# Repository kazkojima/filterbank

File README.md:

# HF filter bamk

KiCad files for a simple HF filter bank.

There are 4 5-order Chebyshev bandpass filters for 0.5-2, 2-10, 10-28, 28-45MHz.
 [Actual characteristics](https://github.com/kazkojima/filterbank/blob/main/images/Figure_1.png) deviate slightly from target values.

A filter is selected with an analog demultiplexer/multiplexer TS3A5017PWR of which select inputs are drived with photo-isolators.

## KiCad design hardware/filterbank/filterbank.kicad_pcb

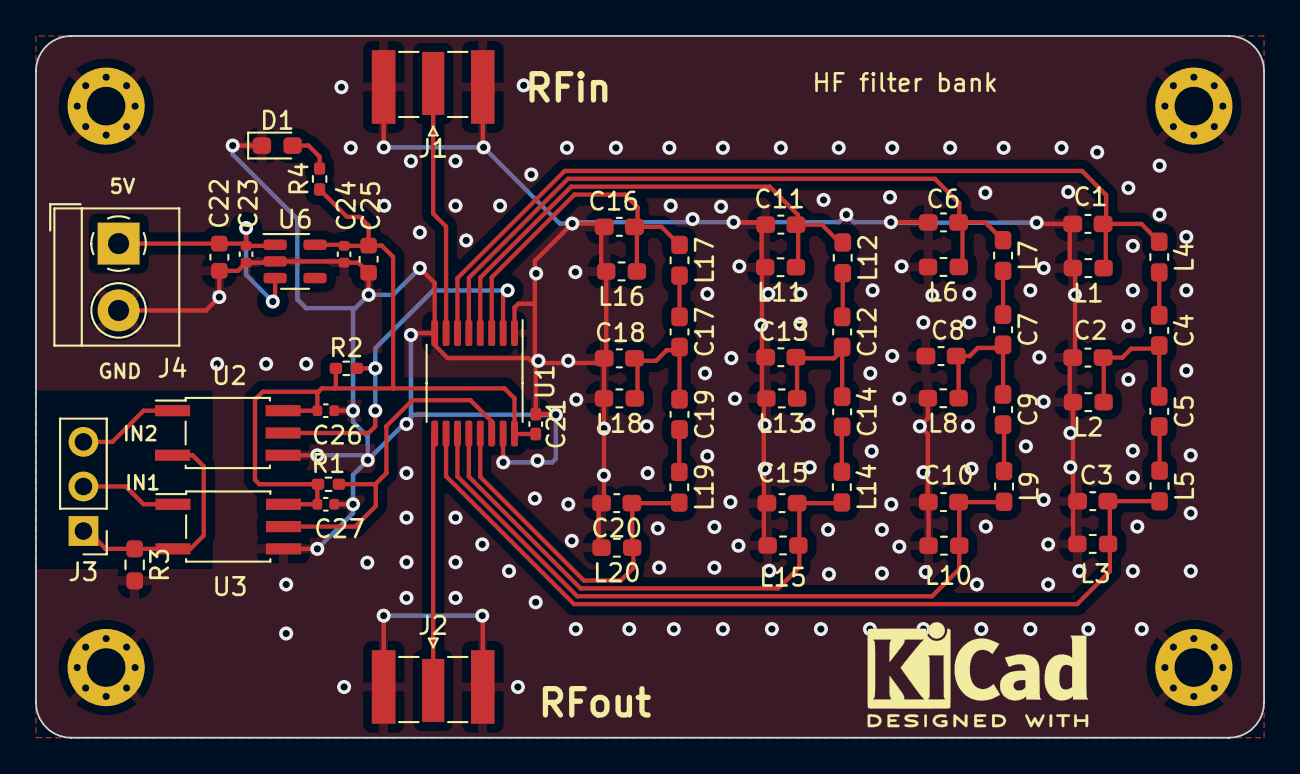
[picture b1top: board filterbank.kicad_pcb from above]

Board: 2 copper layers, 70.0 x 40.0 mm, 64 parts (0 on the bottom side), 31 nets.

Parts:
C1, C3: 2200p; C_0603_1608Metric_Pad1.08x0.95mm_HandSolder
C2: 3900p; C_0603_1608Metric_Pad1.08x0.95mm_HandSolder
C4, C5: 3300p; C_0603_1608Metric_Pad1.08x0.95mm_HandSolder
C6, C10: 470p; C_0603_1608Metric_Pad1.08x0.95mm_HandSolder
C7, C9: 1000p; C_0603_1608Metric_Pad1.08x0.95mm_HandSolder
C8: 820p; C_0603_1608Metric_Pad1.08x0.95mm_HandSolder
C11, C15, C16, C20: 180p; C_0603_1608Metric_Pad1.08x0.95mm_HandSolder
C12, C14: 150p; C_0603_1608Metric_Pad1.08x0.95mm_HandSolder
C13, C18: 330p; C_0603_1608Metric_Pad1.08x0.95mm_HandSolder
C17, C19: 33p; C_0603_1608Metric_Pad1.08x0.95mm_HandSolder
C21: 0.1u; C_0402_1005Metric_Pad0.74x0.62mm_HandSolder
C22, C25: 10u; C_0603_1608Metric
C23, C24: 1u; C_0402_1005Metric
C26, C27: 0.1u; C_0402_1005Metric
D1: LED_Filled; LED_0603_1608Metric_Pad1.05x0.95mm_HandSolder
H1, H2, H3, H4: MountingHole_Pad; MountingHole_2.2mm_M2_Pad_Via
J1, J2: Conn_Coaxial; SMA_Samtec_SMA-J-P-X-ST-EM1_EdgeMount
J3: Conn_01x03; PinHeader_1x03_P2.54mm_Vertical
J4: Screw_Terminal_01x02; TerminalBlock3.81mm
L1, L3: 10uH; L_0603_1608Metric_Pad1.05x0.95mm_HandSolder
L2: 5.6uH; L_0603_1608Metric_Pad1.05x0.95mm_HandSolder
L4, L5: 6.8uH; L_0603_1608Metric_Pad1.05x0.95mm_HandSolder
L6, L10: 2.7uH; L_0603_1608Metric_Pad1.05x0.95mm_HandSolder
L7, L8, L9: 1.5uH; L_0603_1608Metric_Pad1.05x0.95mm_HandSolder
L11, L15: 470nH; L_0603_1608Metric_Pad1.05x0.95mm_HandSolder
L12, L14, L17, L19: 560nH; L_0603_1608Metric_Pad1.05x0.95mm_HandSolder
L13: 270nH; L_0603_1608Metric_Pad1.05x0.95mm_HandSolder
L16, L20: 100nH; L_0603_1608Metric_Pad1.05x0.95mm_HandSolder
L18: 56nH; L_0603_1608Metric_Pad1.05x0.95mm_HandSolder
R1, R2: 4.99k; R_0402_1005Metric_Pad0.72x0.64mm_HandSolder
R3: 10M; R_0603_1608Metric_Pad0.98x0.95mm_HandSolder
R4: 3k; R_0402_1005Metric_Pad0.72x0.64mm_HandSolder
U1: TS3A5017PWR; TSSOP-16_4.4x5mm_P0.65mm
U2, U3: TLP2368; SO-5_4.4x3.6mm_P1.27mm
U6: ADP151AUJZ-3.3; TSOT-23-5

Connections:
+3V3: C21.2, C24.1, C25.1, C26.1, C27.1, R1.1, R2.1, R4.1, U1.16 (V+), U2.6 (VDD), U3.6 (VDD), U6.5 (VOUT)
F1OUT: C3.1, L3.1, L5.2, U1.10 (2S1)
F2OUT: C10.1, L9.2, L10.1, U1.11 (2S2)
F3OUT: C15.1, L14.2, L15.1, U1.12 (2S3)
F4OUT: C20.1, L19.2, L20.1, U1.13 (2S4)
GND: C1.2, C2.2, C3.2, C6.2, C8.2, C10.2, C11.2, C13.2, C15.2, C16.2, C18.2, C20.2, C21.1, C22.2, C23.2, C24.2, C25.2, C26.2, C27.2, D1.1 (K), H1.1, H2.1, H3.1, H4.1, J1.2 (Ext), J2.2 (Ext), J4.2, L1.2, L2.2, L3.2, L6.2, L8.2, L10.2, L11.2, L13.2, L15.2, L16.2, L18.2, L20.2, R3.2, U1.1 (1~EN), U1.8 (GND), U1.15 (2~EN), U2.4 (GND), U3.4 (GND), U6.2 (GND)
unnamed: C2.1, C4.2, C5.1, L2.1
unnamed: C4.1, L4.2
unnamed: C5.2, L5.1
unnamed: C7.1, L7.2
unnamed: C7.2, C8.1, C9.1, L8.1
unnamed: C9.2, L9.1
unnamed: C12.1, L12.2
unnamed: C12.2, C13.1, C14.1, L13.1
unnamed: C14.2, L14.1
unnamed: C17.1, L17.2
unnamed: C17.2, C18.1, C19.1, L18.1
unnamed: C19.2, L19.1
unnamed: D1.2 (A), R4.2
unnamed: J1.1 (In), U1.7 (1D)
unnamed: J2.1 (In), U1.9 (2D)
unnamed: J3.1, R3.1, U2.3 (K), U3.3 (K)
unnamed: J3.2, U3.1 (A)
unnamed: J3.3, U2.1 (A)
unnamed: C22.1, C23.1, J4.1, U6.1 (VIN), U6.3 (EN)
unnamed: C1.1, L1.1, L4.1, U1.6 (1S1)
unnamed: C6.1, L6.1, L7.1, U1.5 (1S2)
unnamed: C11.1, L11.1, L12.1, U1.4 (1S3)
unnamed: C16.1, L16.1, L17.1, U1.3 (1S4)
unnamed: R1.2, U1.14 (IN1), U3.5 (VO)
unnamed: R2.2, U1.2 (IN2), U2.5 (VO)

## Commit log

2023-02-15 Initial commit.
